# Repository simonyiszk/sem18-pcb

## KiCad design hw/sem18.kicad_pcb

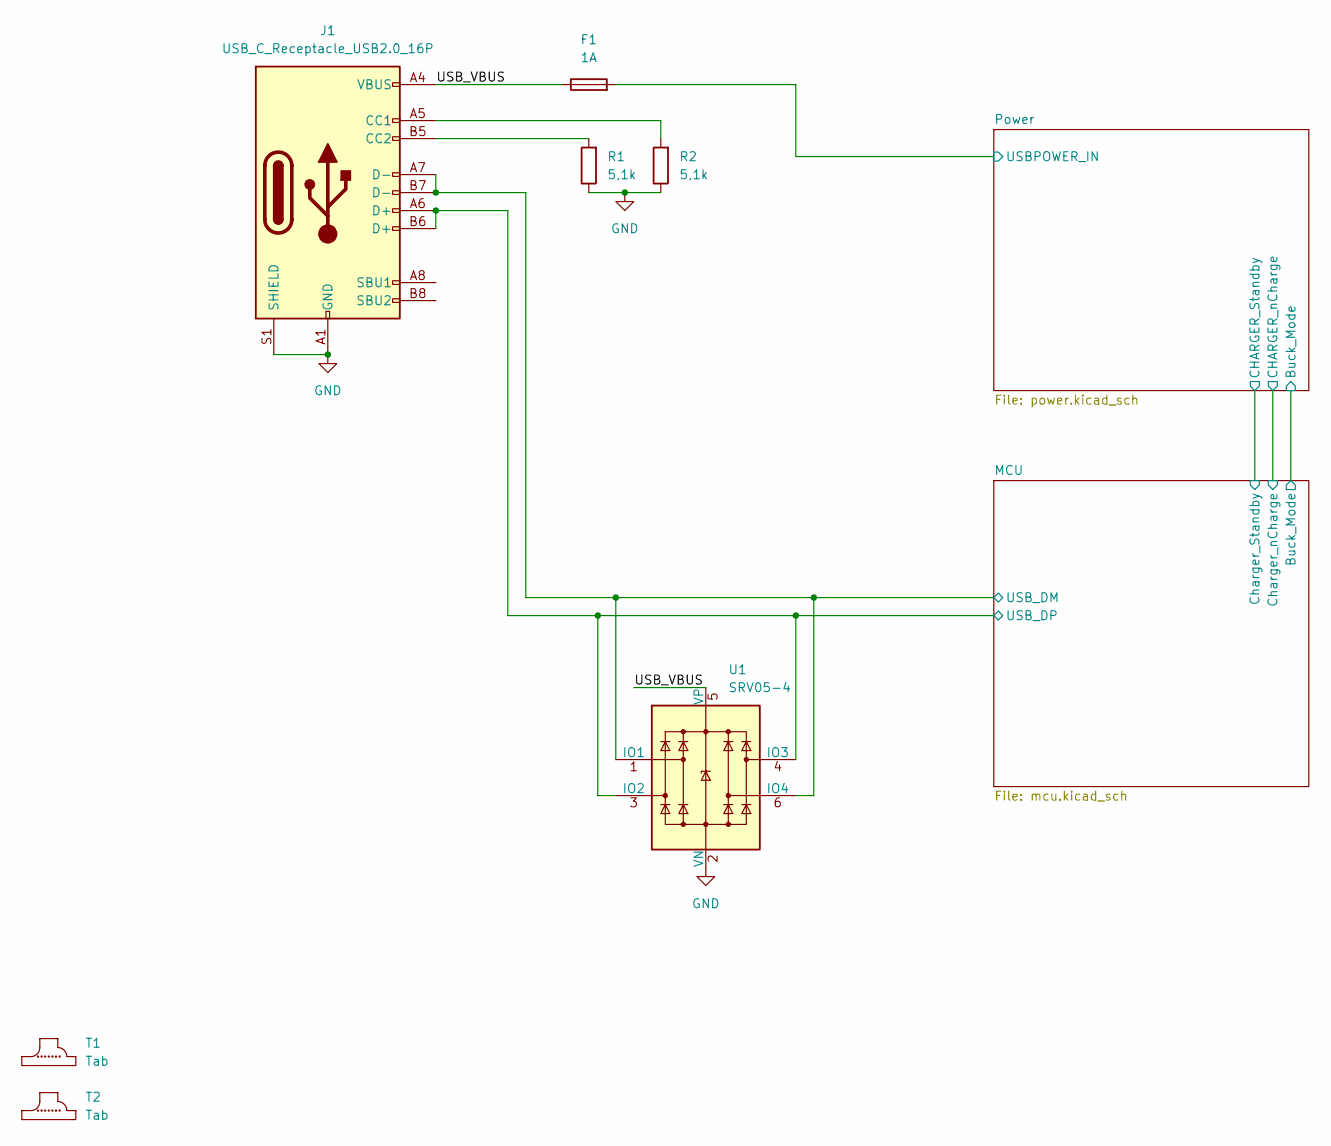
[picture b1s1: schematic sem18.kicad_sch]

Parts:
F1: 1A; Fuse_1206_3216Metric
J1: USB_C_Receptacle_USB2.0_16P; USB_C_Receptacle_G-Switch_GT-USB-7010ASV
R1, R2: 5,1k; R_0603_1608Metric
T1, T2: Tab
U1: SRV05-4; SOT-23-6

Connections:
/MCU/USB_DM: J1.A7 (D-), J1.B7 (D-), U1.1 (IO1), U1.6 (IO4); also elsewhere on the board
/MCU/USB_DP: J1.A6 (D+), J1.B6 (D+), U1.3 (IO2), U1.4 (IO3); also elsewhere on the board
/Power/USBPOWER_IN: F1.2; also elsewhere on the board
/USB_VBUS: F1.1, J1.A4 (VBUS), J1.A9 (VBUS), J1.B4 (VBUS), J1.B9 (VBUS), U1.5 (VP)
GND: J1.A1 (GND), J1.A12 (GND), J1.B1 (GND), J1.B12 (GND), J1.S1 (SHIELD), R1.1, R2.1, U1.2 (VN); also elsewhere on the board
unnamed: J1.A5 (CC1), R2.2
unnamed: J1.B5 (CC2), R1.2

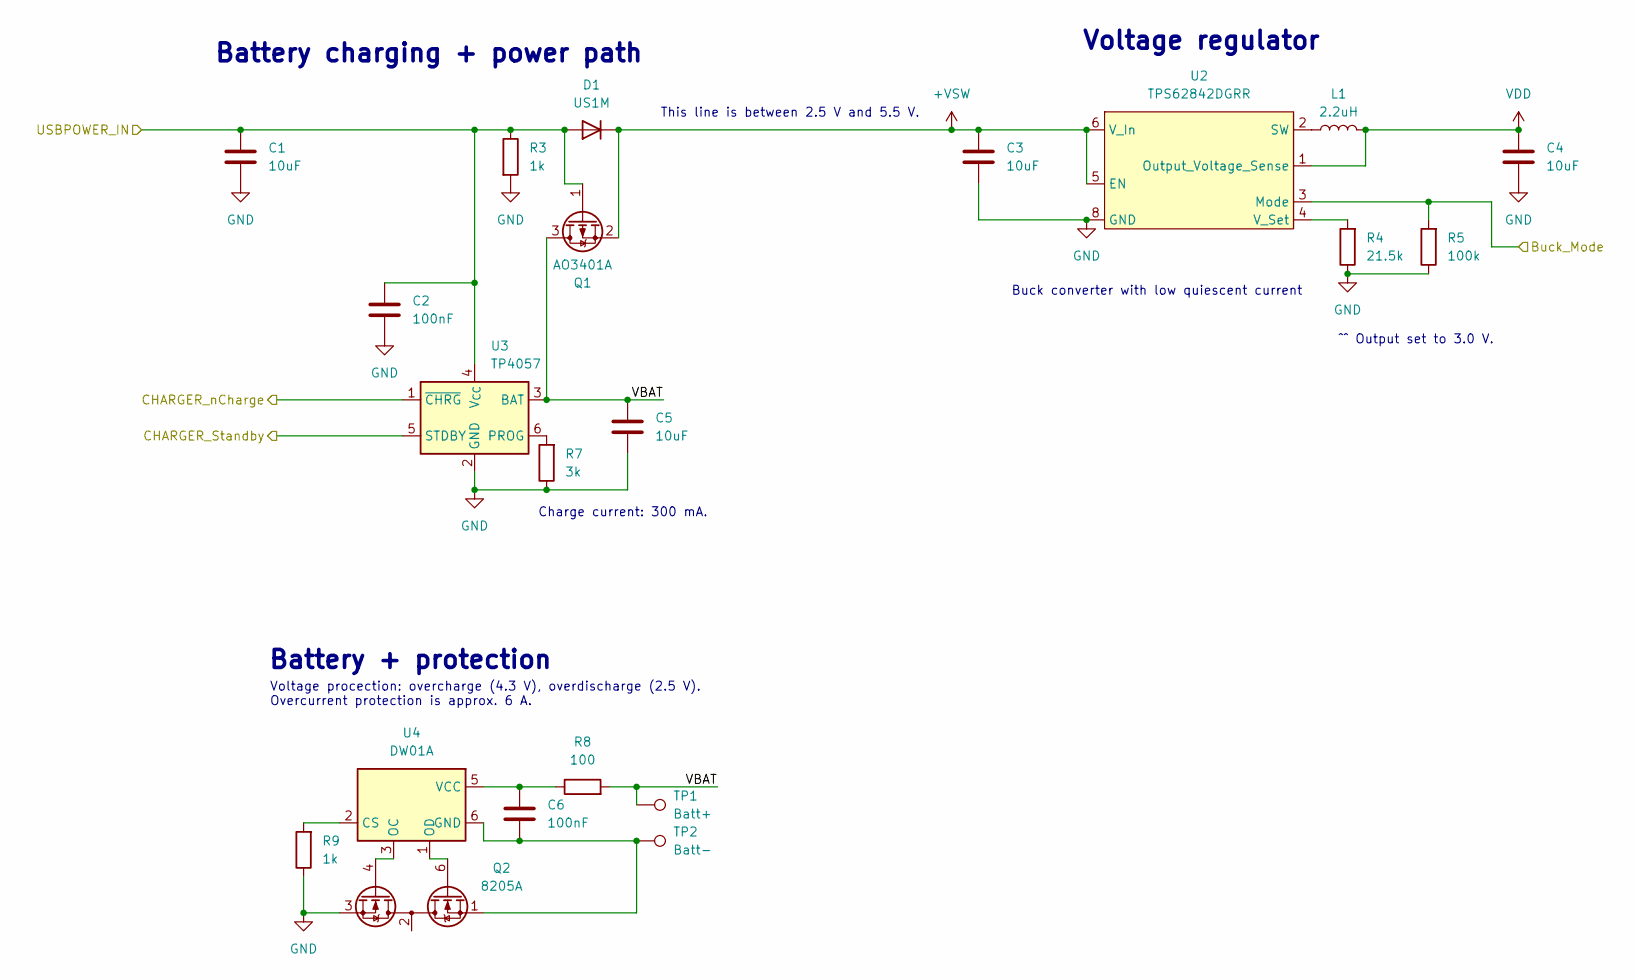
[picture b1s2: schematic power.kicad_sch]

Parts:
C1, C3, C4, C5: 10uF; C_0805_2012Metric
C2, C6: 100nF; C_0603_1608Metric
D1: US1M; D_SMA
L1: 2.2uH; L_APV_ANR3012
Q1: AO3401A; SOT-23
Q2: 8205A; SOT-23-6
R3, R9: 1k; R_0603_1608Metric
R4: 21.5k; R_0603_1608Metric
R5: 100k; R_0603_1608Metric
R7: 3k; R_0603_1608Metric
R8: 100; R_0603_1608Metric
TP1: Batt+; SolderWirePad_1x01_SMD_1x2mm
TP2: Batt-; SolderWirePad_1x01_SMD_1x2mm
U2: TPS62842DGRR; HVSSOP-8-1EP_3x3mm_P0.65mm_EP1.57x1.89mm
U3: TP4057; TSOT-23-6
U4: DW01A; SOT-23-6

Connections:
+VSW: C3.1, D1.1 (K), Q1.2 (S), U2.5 (EN), U2.6 (V_In); also elsewhere on the board
/MCU/Buck_Mode: R5.2, U2.3 (Mode); also elsewhere on the board
/MCU/Charger_Standby: U3.5 (STDBY); also elsewhere on the board
/MCU/Charger_nCharge: U3.1 (~CHRG); also elsewhere on the board
/Power/USBPOWER_IN: C1.1, C2.2, D1.2 (A), Q1.1 (G), R3.1, U3.4 (V_{CC}); also elsewhere on the board
/Power/VBAT: C5.1, Q1.3 (D), R8.2, TP1.1, U3.3 (BAT)
GND: C1.2, C2.1, C3.2, C4.2, C5.2, Q2.3 (S2), R3.2, R4.1, R5.1, R7.1, R9.1, U2.8 (GND), U2.9 (GND), U3.2 (GND); also elsewhere on the board
unnamed: C6.2, Q2.1 (D1), TP2.1, U4.6 (GND)
unnamed: Q2.6 (G1), U4.1 (OD)
unnamed: Q2.4 (G2), U4.3 (OC)
unnamed: Q2.2 (S1/D2), Q2.5 (S1/D2)
unnamed: L1.1, U2.2 (SW)
unnamed: R4.2, U2.4 (V_Set)
unnamed: R7.2, U3.6 (PROG)
unnamed: R9.2, U4.2 (CS)
unnamed: C6.1, R8.1, U4.5 (VCC)
VDD: C4.1, L1.2, U2.1 (Output_Voltage_Sense); also elsewhere on the board

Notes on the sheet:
Buck converter with low quiescent current
Charge current: 300 mA.
Voltage procection: overcharge (4.3 V), overdischarge (2.5 V). Overcurrent protection is approx. 6 A.
This line is between 2.5 V and 5.5 V.
Battery charging + power path
Voltage regulator
^^ Output set to 3.0 V.
Battery + protection

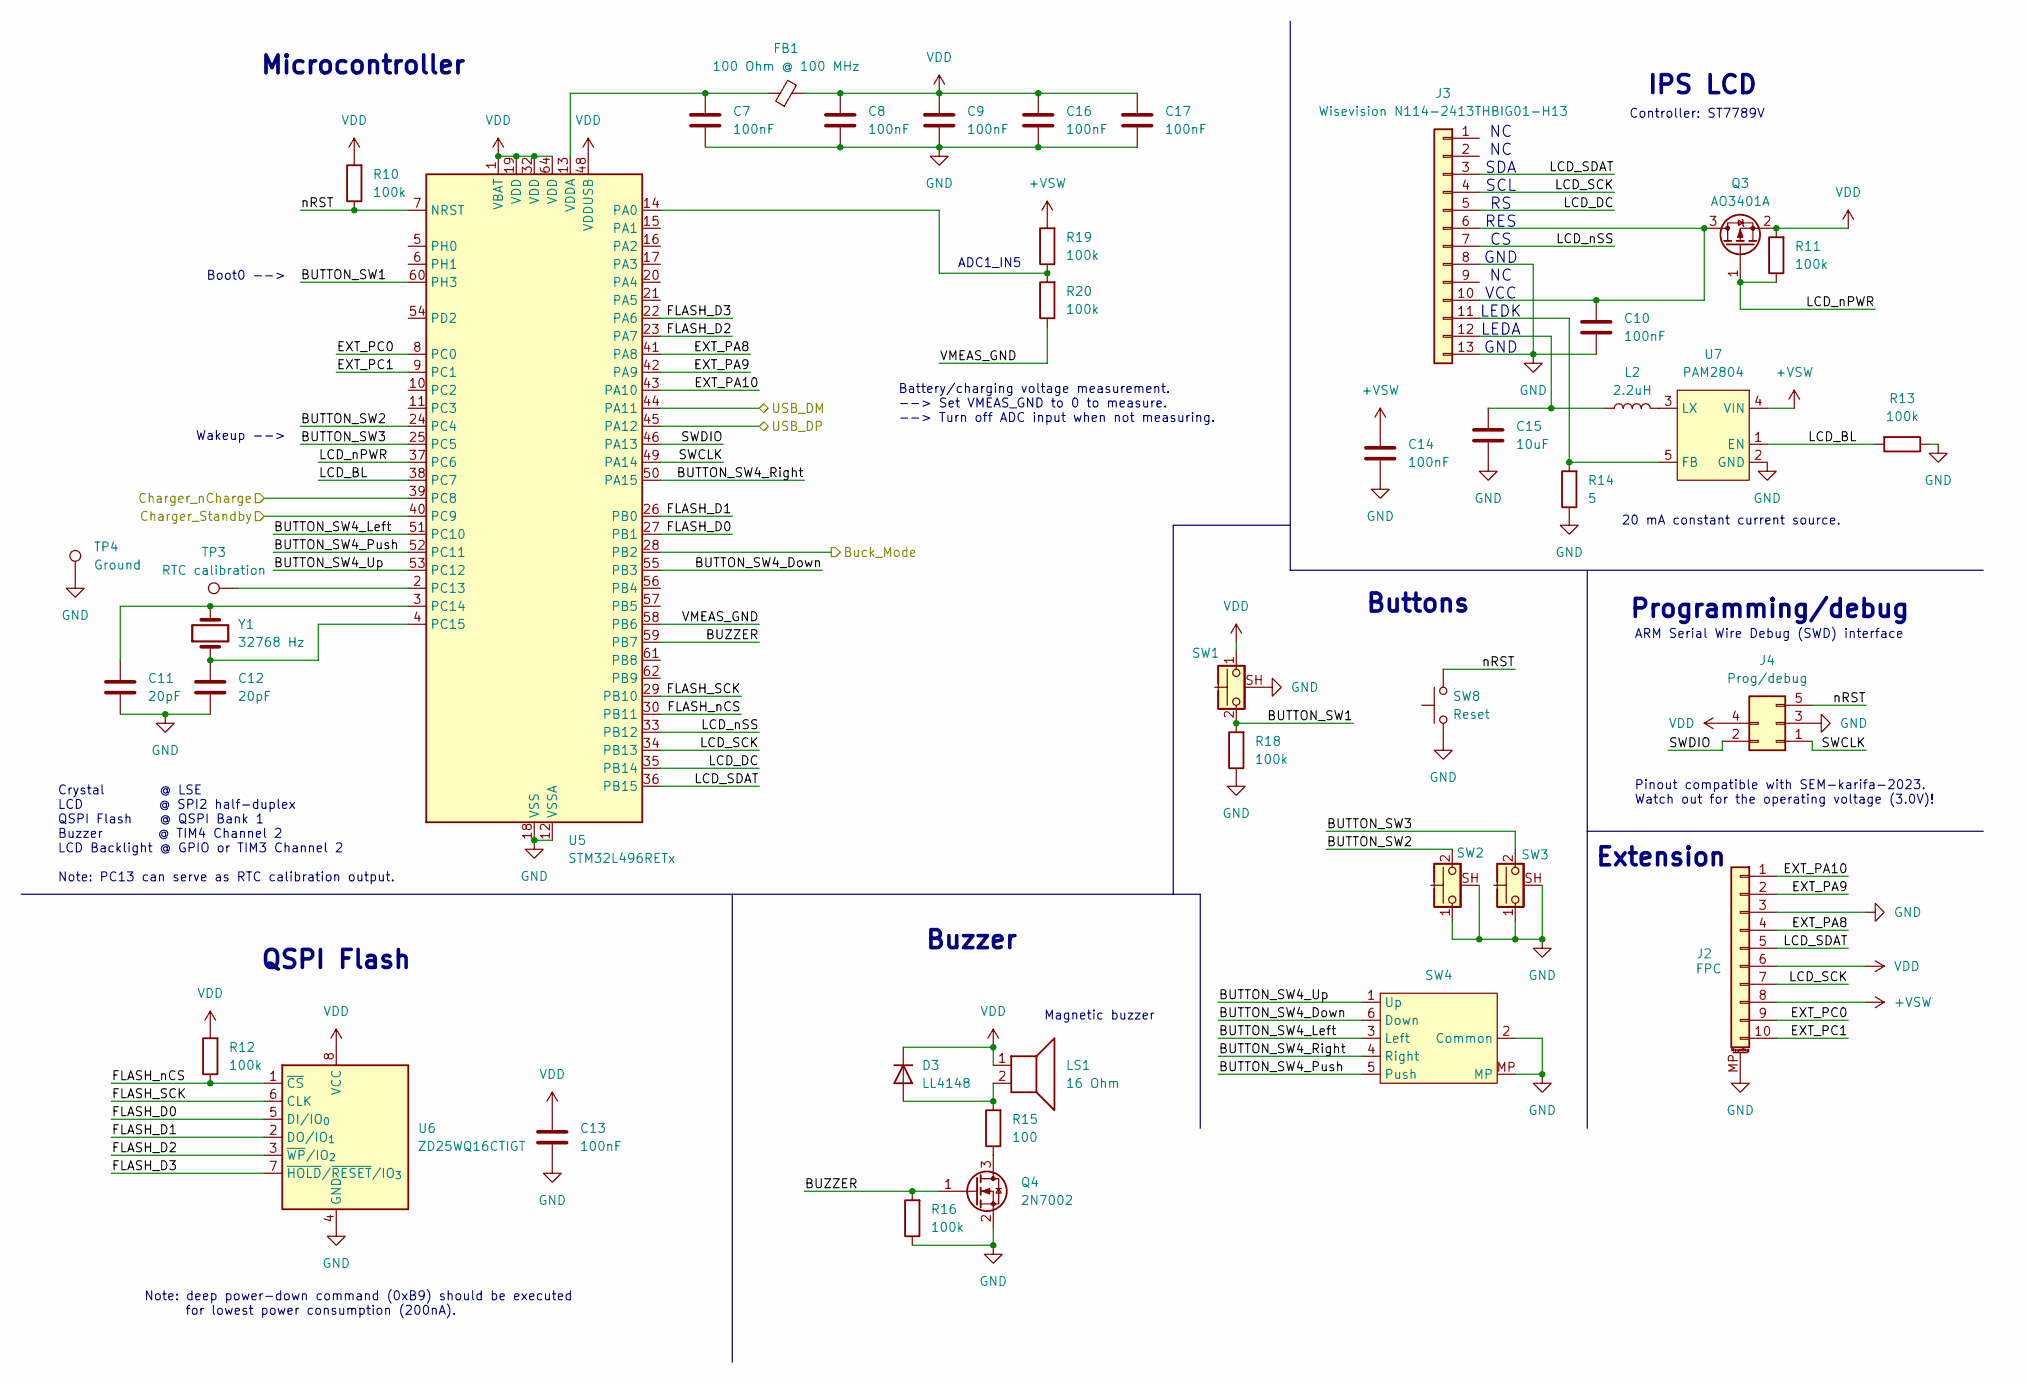
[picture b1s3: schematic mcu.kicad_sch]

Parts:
C7, C8, C9, C10, C13, C14, C16, C17: 100nF; C_0603_1608Metric
C11, C12: 20pF; C_0603_1608Metric
C15: 10uF; C_0805_2012Metric
D3: LL4148; D_MiniMELF
FB1: 100 Ohm @ 100 MHz; L_0805_2012Metric
J2: FPC; Hirose_FH12-10S-0.5SH_1x10-1MP_P0.50mm_Horizontal
J3: Wisevision N114-2413THBIG01-H13; LCD_ST7789V_13pin
J4: Prog/debug; ProgConnector_5pin
L2: 2.2uH; L_APV_ANR3012
LS1: 16 Ohm; Buzzer_8.5x8.5mm
Q3: AO3401A; SOT-23
Q4: 2N7002; SOT-23
R10, R11, R12, R13, R16, R18, R19, R20: 100k; R_0603_1608Metric
R14: 5; R_0603_1608Metric
R15: 100; R_0603_1608Metric
SW1, SW2, SW3: SW_Push_Shielded; SMD_Tactile_Switch_7.7x3.6mm_Right-angle
SW4: SMD_Directional_Switch
SW8: Reset; SW_SPST_TL3342
TP3: RTC calibration; TestPoint_Pad_D1.0mm
TP4: Ground; TestPoint_Pad_D1.0mm
U5: STM32L496RETx; LQFP-64_10x10mm_P0.5mm
U6: ZD25WQ16CTIGT; SOIC-8_5.3x5.3mm_P1.27mm
U7: PAM2804; SOT-23-5
Y1: 32768 Hz; Crystal_DS26_D2.0mm_L6.0mm_Vertical

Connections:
+VSW: C14.2, J2.8, R19.2, U7.4 (VIN); also elsewhere on the board
/MCU/BUTTON_SW1: R18.2, SW1.2, U5.60 (PH3)
/MCU/BUTTON_SW2: SW2.2, U5.24 (PC4)
/MCU/BUTTON_SW3: SW3.2, U5.25 (PC5)
/MCU/BUTTON_SW4_Down: SW4.6 (Down), U5.55 (PB3)
/MCU/BUTTON_SW4_Left: SW4.3 (Left), U5.51 (PC10)
/MCU/BUTTON_SW4_Push: SW4.5 (Push), U5.52 (PC11)
/MCU/BUTTON_SW4_Right: SW4.4 (Right), U5.50 (PA15)
/MCU/BUTTON_SW4_Up: SW4.1 (Up), U5.53 (PC12)
/MCU/BUZZER: Q4.1 (G), R16.2, U5.59 (PB7)
/MCU/Buck_Mode: U5.28 (PB2); also elsewhere on the board
/MCU/Charger_Standby: U5.40 (PC9); also elsewhere on the board
/MCU/Charger_nCharge: U5.39 (PC8); also elsewhere on the board
/MCU/EXT_PA8: J2.4, U5.41 (PA8)
/MCU/EXT_PA9: J2.2, U5.42 (PA9)
/MCU/EXT_PA10: J2.1, U5.43 (PA10)
/MCU/EXT_PC0: J2.9, U5.8 (PC0)
/MCU/EXT_PC1: J2.10, U5.9 (PC1)
/MCU/FLASH_D0: U5.27 (PB1), U6.5 (DI/IO_{0})
/MCU/FLASH_D1: U5.26 (PB0), U6.2 (DO/IO_{1})
/MCU/FLASH_D2: U5.23 (PA7), U6.3 (~WP/IO_{2})
/MCU/FLASH_D3: U5.22 (PA6), U6.7 (~HOLD/~RESET/IO_{3})
/MCU/FLASH_SCK: U5.29 (PB10), U6.6 (CLK)
/MCU/FLASH_nCS: R12.1, U5.30 (PB11), U6.1 (~CS)
/MCU/LCD_BL: R13.2, U5.38 (PC7), U7.1 (EN)
/MCU/LCD_DC: J3.5, U5.35 (PB14)
/MCU/LCD_SCK: J2.7, J3.4, U5.34 (PB13)
/MCU/LCD_SDAT: J2.5, J3.3, U5.36 (PB15)
/MCU/LCD_nPWR: Q3.1 (G), R11.1, U5.37 (PC6)
/MCU/LCD_nSS: J3.7, U5.33 (PB12)
/MCU/SWCLK: J4.1, U5.49 (PA14)
/MCU/SWDIO: J4.2, U5.46 (PA13)
/MCU/USB_DM: U5.44 (PA11); also elsewhere on the board
/MCU/USB_DP: U5.45 (PA12); also elsewhere on the board
/MCU/VMEAS_GND: R20.1, U5.58 (PB6)
/MCU/nRST: J4.5, R10.1, SW8.2, U5.7 (NRST)
GND: C7.1, C8.1, C9.1, C10.1, C11.1, C12.1, C13.1, C14.1, C15.2, C16.1, C17.1, J2.3, J2.MP (MountPin), J3.8, J3.13, J4.3, Q4.2 (S), R13.1, R14.1, R16.1, R18.1, SW1.SH (B), SW2.1, SW2.SH (B), SW3.1, SW3.SH (B), SW4.2 (Common), SW4.MP, SW8.1, TP4.1, U5.12 (VSSA), U5.18 (VSS), U5.31 (VSS), U5.47 (VSS), U5.63 (VSS), U6.4 (GND), U7.2 (GND); also elsewhere on the board
unnamed: D3.2 (A), LS1.2, R15.2
unnamed: C10.2, J3.6, J3.10, Q3.3 (D)
unnamed: J3.11, R14.2, U7.5 (FB)
unnamed: C15.1, J3.12, L2.1
unnamed: Q4.3 (D), R15.1
unnamed: R19.1, R20.2, U5.14 (PA0)
unnamed: TP3.1, U5.2 (PC13)
unnamed: C11.2, U5.3 (PC14), Y1.2
unnamed: C12.2, U5.4 (PC15), Y1.1
unnamed: C7.2, FB1.1, U5.13 (VDDA)
unnamed: L2.2, U7.3 (LX)
VDD: C8.2, C9.2, C13.2, C16.2, C17.2, D3.1 (K), FB1.2, J2.6, J4.4, LS1.1, Q3.2 (S), R10.2, R11.2, R12.2, SW1.1, U5.1 (VBAT), U5.19 (VDD), U5.32 (VDD), U5.48 (VDDUSB), U5.64 (VDD), U6.8 (VCC); also elsewhere on the board

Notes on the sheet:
IPS LCD
Note: deep power-down command (0xB9) should be executed for lowest power consumption (200nA).
Boot0 -->
Extension
Pinout compatible with SEM-karifa-2023. Watch out for the operating voltage (3.0V)!
Crystal @ LSE LCD @ SPI2 half-duplex QSPI Flash @ QSPI Bank 1 Buzzer @ TIM4 Channel 2 LCD Backlight @ GPIO or TIM3 Channel 2 Note: PC13 can serve as RTC calibration output.
Magnetic buzzer
NC NC SDA SCL RS RES CS GND NC VCC LEDK LEDA GND
Buttons
Battery/charging voltage measurement. --> Set VMEAS_GND to 0 to measure. --> Turn off ADC input when not measuring.
Programming/debug
ARM Serial Wire Debug (SWD) interface
Controller: ST7789V
20 mA constant current source.
Buzzer
QSPI Flash
Microcontroller
ADC1_IN5
Wakeup -->

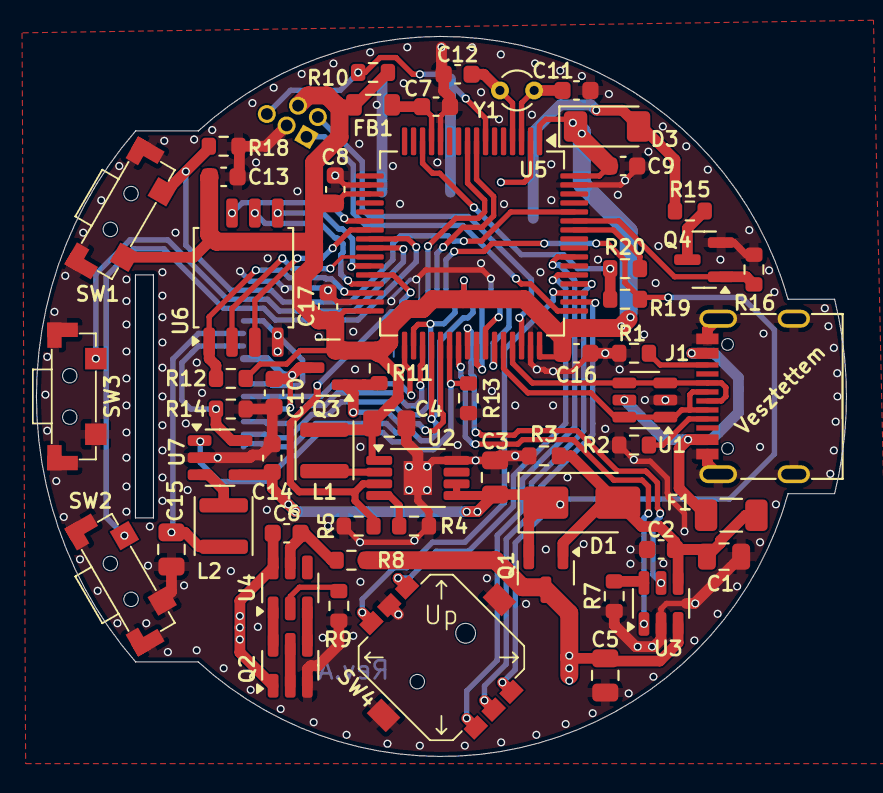
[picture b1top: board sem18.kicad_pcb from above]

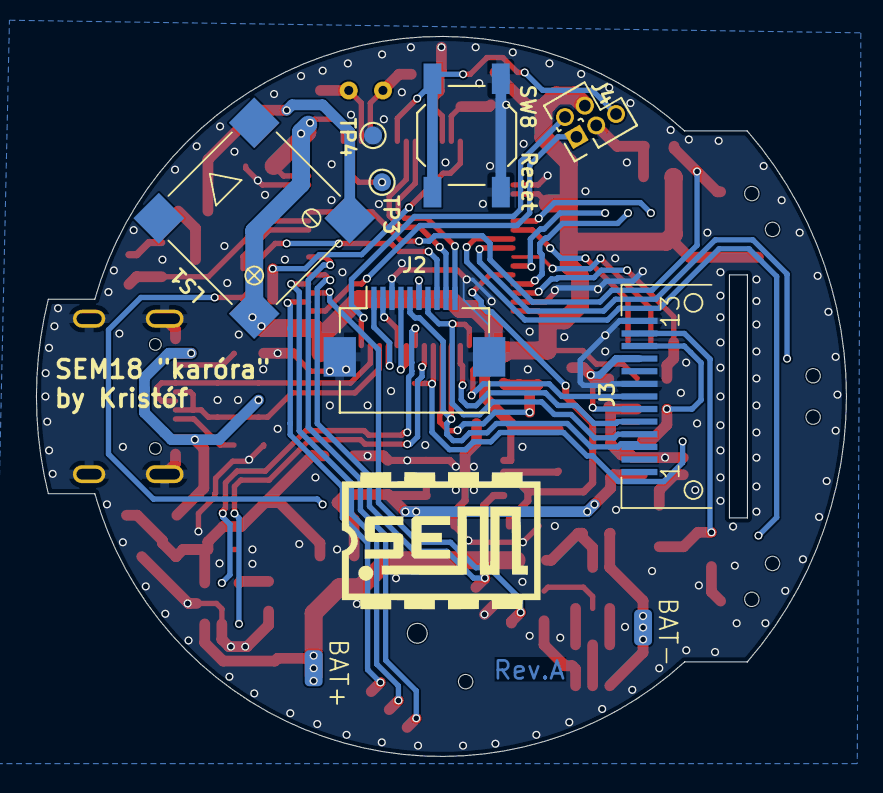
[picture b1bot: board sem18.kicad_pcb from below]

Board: 4 copper layers, 45.0 x 40.0 mm, 69 parts (9 on the bottom side), 63 nets.

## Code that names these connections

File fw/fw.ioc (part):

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Mcu.Name=STM32L496R(E-G)Tx
Mcu.Package=LQFP64
Mcu.UserName=STM32L496RETx
PA0.Signal=ADCx_IN5
PA11.Mode=Device_Only
PA11.Signal=USB_OTG_FS_DM
PA12.Mode=Device_Only
PA12.Signal=USB_OTG_FS_DP
PA13\ (JTMS/SWDIO).Mode=Serial_Wire
PA13\ (JTMS/SWDIO).Signal=SYS_JTMS-SWDIO
PA14\ (JTCK/SWCLK).Mode=Serial_Wire
PA14\ (JTCK/SWCLK).Signal=SYS_JTCK-SWCLK
PA15\ (JTDI).GPIOParameters=GPIO_PuPd,GPIO_Label
PA15\ (JTDI).GPIO_Label=BUTTON_SW4_RIGHT
PA15\ (JTDI).GPIO_PuPd=GPIO_PULLUP
PA15\ (JTDI).Signal=GPIO_Input
PA6.GPIOParameters=GPIO_PuPd
PA6.GPIO_PuPd=GPIO_PULLUP
PA6.Mode=Single Bank 1
PA6.Signal=QUADSPI_BK1_IO3
PA7.GPIOParameters=GPIO_PuPd
PA7.GPIO_PuPd=GPIO_PULLUP
PA7.Mode=Single Bank 1
PA7.Signal=QUADSPI_BK1_IO2
PB0.GPIOParameters=GPIO_PuPd
PB0.GPIO_PuPd=GPIO_PULLUP
PB0.Mode=Single Bank 1
PB0.Signal=QUADSPI_BK1_IO1
PB1.GPIOParameters=GPIO_PuPd
PB1.GPIO_PuPd=GPIO_PULLUP
PB1.Mode=Single Bank 1
PB1.Signal=QUADSPI_BK1_IO0
PB10.Mode=Single Bank 1
PB10.Signal=QUADSPI_CLK
PB11.Mode=Single Bank 1
PB11.Signal=QUADSPI_BK1_NCS
PB12.GPIOParameters=GPIO_Speed,PinState,GPIO_Label
PB12.GPIO_Label=LCD_nSS
PB12.GPIO_Speed=GPIO_SPEED_FREQ_VERY_HIGH
PB12.PinState=GPIO_PIN_SET
PB12.Signal=GPIO_Output
PB13.Mode=Simplex_Bidirectional_Master
PB13.Signal=SPI2_SCK
PB14.GPIOParameters=GPIO_Label
PB14.GPIO_Label=LCD_DC
PB14.Signal=GPIO_Output
PB15.Mode=Simplex_Bidirectional_Master
PB15.Signal=SPI2_MOSI
PB2.GPIOParameters=GPIO_Speed,GPIO_Label
PB2.GPIO_Label=BUCK_MODE
PB2.GPIO_Speed=GPIO_SPEED_FREQ_MEDIUM
PB2.Signal=GPIO_Output
PB3\ (JTDO/TRACESWO).GPIOParameters=GPIO_PuPd,GPIO_Label
PB3\ (JTDO/TRACESWO).GPIO_Label=BUTTON_SW4_DOWN
PB3\ (JTDO/TRACESWO).GPIO_PuPd=GPIO_PULLUP
PB3\ (JTDO/TRACESWO).Signal=GPIO_Input
PB6.GPIOParameters=GPIO_Speed,PinState,GPIO_PuPd,GPIO_Label,GPIO_ModeDefaultOutputPP
PB6.GPIO_Label=VMEAS_GND
PB6.GPIO_ModeDefaultOutputPP=GPIO_MODE_OUTPUT_OD
PB6.GPIO_PuPd=GPIO_NOPULL
PB6.GPIO_Speed=GPIO_SPEED_FREQ_VERY_HIGH
PB6.PinState=GPIO_PIN_SET
PB6.Signal=GPIO_Output
PB7.GPIOParameters=GPIO_Speed,GPIO_Label
PB7.GPIO_Label=BUZZER
PB7.GPIO_Speed=GPIO_SPEED_FREQ_HIGH
PB7.Signal=S_TIM4_CH2
PC10.GPIOParameters=GPIO_PuPd,GPIO_Label
PC10.GPIO_Label=BUTTON_SW4_LEFT
PC10.GPIO_PuPd=GPIO_PULLUP
PC10.Signal=GPIO_Input
PC11.GPIOParameters=GPIO_PuPd,GPIO_Label
PC11.GPIO_Label=BUTTON_SW4_PUSH
PC11.GPIO_PuPd=GPIO_PULLUP
PC11.Signal=GPIO_Input
PC12.GPIOParameters=GPIO_PuPd,GPIO_Label
PC12.GPIO_Label=BUTTON_SW4_UP
PC12.GPIO_PuPd=GPIO_PULLUP
PC12.Signal=GPIO_Input
PC14-OSC32_IN\ (PC14).Mode=LSE-External-Oscillator
PC14-OSC32_IN\ (PC14).Signal=RCC_OSC32_IN
PC15-OSC32_OUT\ (PC15).Mode=LSE-External-Oscillator
PC15-OSC32_OUT\ (PC15).Signal=RCC_OSC32_OUT
PC4.GPIOParameters=GPIO_PuPd,GPIO_Label
PC4.GPIO_Label=BUTTON_SW2
PC4.GPIO_PuPd=GPIO_PULLUP
PC4.Signal=GPIO_Input
PC5.GPIOParameters=GPIO_PuPd,GPIO_Label
PC5.GPIO_Label=BUTTON_SW3
PC5.GPIO_PuPd=GPIO_PULLUP
PC5.Signal=GPIO_Input
PC6.GPIOParameters=GPIO_Speed,PinState,GPIO_PuPd,GPIO_Label,GPIO_ModeDefaultOutputPP
PC6.GPIO_Label=LCD_nPWR
PC6.GPIO_ModeDefaultOutputPP=GPIO_MODE_OUTPUT_OD
PC6.GPIO_PuPd=GPIO_NOPULL
PC6.GPIO_Speed=GPIO_SPEED_FREQ_MEDIUM
PC6.PinState=GPIO_PIN_SET
PC6.Signal=GPIO_Output
PC7.GPIOParameters=GPIO_Speed,GPIO_Label
PC7.GPIO_Label=LCD_BL
PC7.GPIO_Speed=GPIO_SPEED_FREQ_MEDIUM
PC7.Signal=GPIO_Output
PC8.GPIOParameters=GPIO_PuPd,GPIO_Label
PC8.GPIO_Label=CHARGER_nCHARGE
PC8.GPIO_PuPd=GPIO_PULLUP
PC8.Signal=GPIO_Input
PC9.GPIOParameters=GPIO_PuPd,GPIO_Label
PC9.GPIO_Label=CHARGER_STANDBY
PC9.GPIO_PuPd=GPIO_PULLUP
PC9.Signal=GPIO_Input
PH3-BOOT0.GPIOParameters=GPIO_PuPd,GPIO_Label,GPIO_ModeDefaultEXTI
PH3-BOOT0.GPIO_Label=BUTTON_SW1
PH3-BOOT0.GPIO_ModeDefaultEXTI=GPIO_MODE_IT_RISING
PH3-BOOT0.GPIO_PuPd=GPIO_PULLDOWN
PH3-BOOT0.Signal=GPIO_Input
RCC.HSE_VALUE=8000000
RCC.SYSCLKFreq_VALUE=80000000
RCC.SYSCLKSource=RCC_SYSCLKSOURCE_PLLCLK
board=custom

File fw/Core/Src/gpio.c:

/* USER CODE BEGIN Header */
/**
  ******************************************************************************
  * @file    gpio.c
  * @brief   This file provides code for the configuration
  *          of all used GPIO pins.
  ******************************************************************************
  * @attention
  *
  * Copyright (c) 2026 STMicroelectronics.
  * All rights reserved.
  *
  * This software is licensed under terms that can be found in the LICENSE file
  * in the root directory of this software component.
  * If no LICENSE file comes with this software, it is provided AS-IS.
  *
  ******************************************************************************
  */
/* USER CODE END Header */

/* Includes ------------------------------------------------------------------*/
#include "gpio.h"

/* USER CODE BEGIN 0 */

/* USER CODE END 0 */

/*----------------------------------------------------------------------------*/
/* Configure GPIO                                                             */
/*----------------------------------------------------------------------------*/
/* USER CODE BEGIN 1 */

/* USER CODE END 1 */

/** Configure pins as
        * Analog
        * Input
        * Output
        * EVENT_OUT
        * EXTI
        * Free pins are configured automatically as Analog (this feature is enabled through
        * the Code Generation settings)
*/
void MX_GPIO_Init(void)
{

  GPIO_InitTypeDef GPIO_InitStruct = {0};

  /* GPIO Ports Clock Enable */
  __HAL_RCC_GPIOC_CLK_ENABLE();
  __HAL_RCC_GPIOA_CLK_ENABLE();
  __HAL_RCC_GPIOB_CLK_ENABLE();
  __HAL_RCC_GPIOH_CLK_ENABLE();

  /*Configure GPIO pin Output Level */
  HAL_GPIO_WritePin(GPIOB, BUCK_MODE_Pin|LCD_DC_Pin, GPIO_PIN_RESET);

  /*Configure GPIO pin Output Level */
  HAL_GPIO_WritePin(GPIOB, LCD_nSS_Pin|VMEAS_GND_Pin, GPIO_PIN_SET);

  /*Configure GPIO pin Output Level */
  HAL_GPIO_WritePin(LCD_nPWR_GPIO_Port, LCD_nPWR_Pin, GPIO_PIN_SET);

  /*Configure GPIO pin Output Level */
  HAL_GPIO_WritePin(LCD_BL_GPIO_Port, LCD_BL_Pin, GPIO_PIN_RESET);

  /*Configure GPIO pins : PC13 PC0 PC1 */
  GPIO_InitStruct.Pin = GPIO_PIN_13|GPIO_PIN_0|GPIO_PIN_1;
  GPIO_InitStruct.Mode = GPIO_MODE_ANALOG;
  GPIO_InitStruct.Pull = GPIO_NOPULL;
  HAL_GPIO_Init(GPIOC, &GPIO_InitStruct);

  /*Configure GPIO pins : BUTTON_SW2_Pin BUTTON_SW3_Pin CHARGER_nCHARGE_Pin CHARGER_STANDBY_Pin
                           BUTTON_SW4_LEFT_Pin BUTTON_SW4_PUSH_Pin BUTTON_SW4_UP_Pin */
  GPIO_InitStruct.Pin = BUTTON_SW2_Pin|BUTTON_SW3_Pin|CHARGER_nCHARGE_Pin|CHARGER_STANDBY_Pin
                          |BUTTON_SW4_LEFT_Pin|BUTTON_SW4_PUSH_Pin|BUTTON_SW4_UP_Pin;
  GPIO_InitStruct.Mode = GPIO_MODE_INPUT;
  GPIO_InitStruct.Pull = GPIO_PULLUP;
  HAL_GPIO_Init(GPIOC, &GPIO_InitStruct);

  /*Configure GPIO pin : BUCK_MODE_Pin */
  GPIO_InitStruct.Pin = BUCK_MODE_Pin;
  GPIO_InitStruct.Mode = GPIO_MODE_OUTPUT_PP;
  GPIO_InitStruct.Pull = GPIO_NOPULL;
  GPIO_InitStruct.Speed = GPIO_SPEED_FREQ_MEDIUM;
  HAL_GPIO_Init(BUCK_MODE_GPIO_Port, &GPIO_InitStruct);

  /*Configure GPIO pin : LCD_nSS_Pin */
  GPIO_InitStruct.Pin = LCD_nSS_Pin;
  GPIO_InitStruct.Mode = GPIO_MODE_OUTPUT_PP;
  GPIO_InitStruct.Pull = GPIO_NOPULL;
  GPIO_InitStruct.Speed = GPIO_SPEED_FREQ_VERY_HIGH;
  HAL_GPIO_Init(LCD_nSS_GPIO_Port, &GPIO_InitStruct);

  /*Configure GPIO pin : LCD_DC_Pin */
  GPIO_InitStruct.Pin = LCD_DC_Pin;
  GPIO_InitStruct.Mode = GPIO_MODE_OUTPUT_PP;
  GPIO_InitStruct.Pull = GPIO_NOPULL;
  GPIO_InitStruct.Speed = GPIO_SPEED_FREQ_LOW;
  HAL_GPIO_Init(LCD_DC_GPIO_Port, &GPIO_InitStruct);

  /*Configure GPIO pin : LCD_nPWR_Pin */
  GPIO_InitStruct.Pin = LCD_nPWR_Pin;
  GPIO_InitStruct.Mode = GPIO_MODE_OUTPUT_OD;
  GPIO_InitStruct.Pull = GPIO_NOPULL;
  GPIO_InitStruct.Speed = GPIO_SPEED_FREQ_MEDIUM;
  HAL_GPIO_Init(LCD_nPWR_GPIO_Port, &GPIO_InitStruct);

  /*Configure GPIO pin : LCD_BL_Pin */
  GPIO_InitStruct.Pin = LCD_BL_Pin;
  GPIO_InitStruct.Mode = GPIO_MODE_OUTPUT_PP;
  GPIO_InitStruct.Pull = GPIO_NOPULL;
  GPIO_InitStruct.Speed = GPIO_SPEED_FREQ_MEDIUM;
  HAL_GPIO_Init(LCD_BL_GPIO_Port, &GPIO_InitStruct);

  /*Configure GPIO pins : PA8 PA9 PA10 */
  GPIO_InitStruct.Pin = GPIO_PIN_8|GPIO_PIN_9|GPIO_PIN_10;
  GPIO_InitStruct.Mode = GPIO_MODE_ANALOG;
  GPIO_InitStruct.Pull = GPIO_NOPULL;
  HAL_GPIO_Init(GPIOA, &GPIO_InitStruct);

  /*Configure GPIO pin : BUTTON_SW4_RIGHT_Pin */
  GPIO_InitStruct.Pin = BUTTON_SW4_RIGHT_Pin;
  GPIO_InitStruct.Mode = GPIO_MODE_INPUT;
  GPIO_InitStruct.Pull = GPIO_PULLUP;
  HAL_GPIO_Init(BUTTON_SW4_RIGHT_GPIO_Port, &GPIO_InitStruct);

  /*Configure GPIO pin : BUTTON_SW4_DOWN_Pin */
  GPIO_InitStruct.Pin = BUTTON_SW4_DOWN_Pin;
  GPIO_InitStruct.Mode = GPIO_MODE_INPUT;
  GPIO_InitStruct.Pull = GPIO_PULLUP;
  HAL_GPIO_Init(BUTTON_SW4_DOWN_GPIO_Port, &GPIO_InitStruct);

  /*Configure GPIO pin : VMEAS_GND_Pin */
  GPIO_InitStruct.Pin = VMEAS_GND_Pin;
  GPIO_InitStruct.Mode = GPIO_MODE_OUTPUT_OD;
  GPIO_InitStruct.Pull = GPIO_NOPULL;
  GPIO_InitStruct.Speed = GPIO_SPEED_FREQ_VERY_HIGH;
  HAL_GPIO_Init(VMEAS_GND_GPIO_Port, &GPIO_InitStruct);

  /*Configure GPIO pin : BUTTON_SW1_Pin */
  GPIO_InitStruct.Pin = BUTTON_SW1_Pin;
  GPIO_InitStruct.Mode = GPIO_MODE_INPUT;
  GPIO_InitStruct.Pull = GPIO_PULLDOWN;
  HAL_GPIO_Init(BUTTON_SW1_GPIO_Port, &GPIO_InitStruct);

}

/* USER CODE BEGIN 2 */

/* USER CODE END 2 */

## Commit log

2026-03-28 Initial commit.
2026-03-31 Added different voltage regulator.
2026-04-02 Schematic is finished. Needs some touch-ups and component selection (esp. for switches).
2026-04-02 Ignore backups.
2026-04-07 Different microcontroller. Placed most of the components too.
2026-04-07 Placed remaining components.
2026-04-07 Replaced extension connector.
2026-04-08 Routing in progress.
2026-04-09 Routed.
2026-04-09 Supposedly finished.
2026-04-10 Sent to fab.
2026-05-06 Works.
2026-05-07 Added test project.
2026-05-08 Changed naming of the upper left button.
